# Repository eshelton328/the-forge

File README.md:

# The Forge

Hardware design monorepo for KiCad PCB projects with automated CI/CD.

## Repository Structure

```
the-forge/
├── Makefile          # make check / erc / drc / fab-drc
├── boards/           # Individual board projects
│   ├── esp32s3-devkit/        # ESP32-S3 development board
│   ├── esp32s3-devkit-5v/     # ESP32-S3 board, dual 3.3V + 5V rails (WIP)
│   └── tps63070-breakout/   # TPS63070 buck-boost breakout
├── fab-rules/        # DRC rule templates per fab house
├── kibot/            # KiBot output generation configs
├── libs/             # Shared libraries (symbols, footprints, 3D models)
├── scripts/          # Automation scripts
├── emi/              # openEMS + gerber2ems (FDTD / EMI-adjacent smoke; see emi/README.md)
└── .github/workflows # CI/CD pipelines
```

## Boards

| Board | Description | Layers | Status |
|-------|-------------|--------|--------|
| [esp32s3-devkit](boards/esp32s3-devkit/) | ESP32-S3-WROOM-1 dev board with TPS63070 buck-boost, USB-C | 4 | In Development |
| [esp32s3-devkit-5v](boards/esp32s3-devkit-5v/) | ESP32-S3 board with dual TPS63070 rails (3.3V + 5V), RV-3028 RTC, USB-C | 4 | WIP — schematic in progress |
| [tps63070-breakout](boards/tps63070-breakout/) | TPS63070 3.3V buck-boost breakout board | 2 | Migrated |

## CI/CD Pipeline

Every pull request automatically runs:
- **PR title** must follow [Conventional Commits](https://www.conventionalcommits.org/) (e.g. `feat:`, `fix:`, `chore:`, `ci:`)
- **`pytest`** on `tests/` (Python **3.12**; see [`.github/workflows/pytest.yml`](.github/workflows/pytest.yml) — Spice integration cases skip unless `ngspice`/Docker exist)
- **Open-source EMS (openEMS + gerber2ems)** — optional path-filtered workflow ([`.github/workflows/emi-checks.yml`](.github/workflows/emi-checks.yml)): builds pinned **openEMS** + **gerber2ems** and runs an upstream example slice ([`emi/README.md`](emi/README.md)); not every PR
- **ERC** (Electrical Rules Check) on schematics
- **DRC** (Design Rules Check) against multiple fab house rules (JLCPCB, PCBWay)

The KiCad workflow always runs, but it only **executes** ERC/DRC for boards that are in scope: changes under `boards/<name>/` check only those boards, while changes to `libs/`, `fab-rules/`, `kibot/`, `scripts/`, the root `Makefile`, or `.github/workflows/pr-checks.yml` trigger checks on all boards. Doc-only diffs (e.g. just `README.md`) skip the heavy KiCad jobs to save time. **`pytest`** (see **`pytest.yml`**) runs on every PR regardless, so Python regressions cannot slip through doc-only merges.

On release tags, the pipeline generates:
- Fab-ready Gerber/drill ZIPs per fab house
- BOM and component placement files
- Schematic PDFs and board renders

## Local Development

### Prerequisites

```bash
brew install --cask kicad    # KiCad 10 (includes kicad-cli)
pip install kibot kikit       # Automation tools
```

### Running checks locally

From the repository root, the **Makefile** is the usual entry point. **Each command checks one board** — the one named by `BOARD` (default: `esp32s3-devkit`). Nothing scans every board unless you ask for that explicitly.

```bash
make help           # list targets
make list-boards    # show board folder names you can pass as BOARD=...

# Default single board (esp32s3-devkit)
make check
make drc

# A different board — either form (folder and .kicad_* basename must match)
make drc BOARD=other-board
make drc other-board
make check other-board

# Optional: run make check for every board under boards/ (e.g. before a release)
make check-all
```

`kicad-cli` is picked up from your `PATH` if present; on macOS it falls back to
`/Applications/KiCad/KiCad.app/Contents/MacOS/kicad-cli`. Override with
`KICAD_CLI=/path/to/kicad-cli make check`.

### Python tests (pytest)

```bash
pip install -r requirements.txt
python3 -m pytest tests/
```

With **`ngspice`** and **Docker** available, `tests/test_spice_run_sim_integration.py` runs end-to-end Spice smoke; otherwise those cases are **skipped** (same as default CI for `pytest.yml`).

**SPICE / simulation (boards with `sim.yml`):** CI builds [`sim/docker/Dockerfile`](sim/docker/Dockerfile) — same KiCad digest as ERC/DRC plus pinned **ngspice** and the repo **`requirements.txt`** — and runs export + `run_sim.py` inside that image ([`sim/README.md`](sim/README.md)). Local parity: **`make sim-board-docker BOARD=tps63070-breakout`** or **`scripts/sim/run-spice-in-docker.sh --board …`**.

Raw commands (equivalent to the Makefile):

```bash
kicad-cli sch erc --exit-code-violations --format json -o boards/esp32s3-devkit/erc.json \
  boards/esp32s3-devkit/esp32s3-devkit.kicad_sch

kicad-cli pcb drc --exit-code-violations --refill-zones --schematic-parity --format json \
  -o boards/esp32s3-devkit/drc-default.json boards/esp32s3-devkit/esp32s3-devkit.kicad_pcb

./scripts/run-drc-all-fabs.sh boards/esp32s3-devkit
```

### Adding a new board

1. Create a new directory under `boards/`
2. Add a `board.yml` with layer count and fab targets
3. If using shared libraries, create project-local `fp-lib-table` / `sym-lib-table` pointing to `../../libs/`
4. Push a PR -- CI will automatically run checks

## Fab House Rules

DRC rules for each fab house are stored in `fab-rules/` as `.kicad_dru` files. CI swaps these in and runs DRC to tell you which fabs your design is compatible with.

2-layer and 4-layer rules each come in two tiers where noted: **standard** (baseline process) vs **advanced** (tighter vias/clearances, typically higher cost). Each board declares which rule keys it runs in `board.yml`.

| Fab House | Rule File | Notes |
|-----------|-----------|-------|
| JLCPCB 2L Standard | `jlcpcb-2layer-standard.kicad_dru` | 0.3mm via drill, 0.15mm annular ring |
| JLCPCB 2L Advanced | `jlcpcb-2layer-advanced.kicad_dru` | 0.2mm via drill, 0.1mm annular ring |
| JLCPCB 4L Standard | `jlcpcb-4layer.kicad_dru` | |
| JLCPCB 4L Advanced | `jlcpcb-4layer-advanced.kicad_dru` | Tighter annular / hole clearance / pad-track clearance vs standard 4L |
| PCBWay 2L Standard | `pcbway-2layer-standard.kicad_dru` | 0.3mm via drill, 0.45mm via pad |
| PCBWay 2L Advanced | `pcbway-2layer-advanced.kicad_dru` | 0.2mm via drill, 0.35mm via pad |
| PCBWay 4L Standard | `pcbway-4layer.kicad_dru` | |
| PCBWay 4L Advanced | `pcbway-4layer-advanced.kicad_dru` | 0.2mm via drill, 0.35mm via pad vs standard 4L |

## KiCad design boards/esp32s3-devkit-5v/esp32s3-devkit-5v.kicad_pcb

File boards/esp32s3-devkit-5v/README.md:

# ESP32-S3 DevKit with switched 5 V audio rail

Fully routed **64 × 56 mm, four-layer engineering prototype**, revised 2026-09-04. The compact layout is **35.42% smaller** than the previous 74 × 75 mm board. The four buttons retain 15 mm spacing and the component-side order **VOL− / MODE / VOL+ / BATTERY**.

Battery J1 feeds an AO3401A reverse-polarity stage and two TPS63070 buck-boost regulators: 3.307 V for the ESP32-S3/RTC and 4.985 V for the MAX98357A amplifier. GPIO18 enables the audio rail. USB-C is data-only. The RTC, switched OLED bus, wake buttons and common-anode RGB indicator remain.

The converter cells keep the nearest input/output ceramics beside the power pins, with their ground pads facing north. Their power-pad centers are 1.81 mm from VIN/VOUT, with direct 0.4 mm top-side connections. Explicit quiet feedback/VAUX returns and two nearby PGND plane connections per converter are retained. The amplifier sits beside the speaker connector. Both speaker traces are 5.37 mm long, entirely on F.Cu, with 0.6 mm main conductors and short 0.2 mm package escapes; neither uses vias. In1.Cu remains the ground reference.

New monitoring hardware provides positive USB-presence detection on GPIO7, switched battery-voltage sensing on GPIO2/ADC1 with GPIO12 enable, and converter power-good inputs on GPIO15/13. Both PG pull-ups use 3.3 V. Eight labeled underside test pads expose ground, protected battery, both rails, enables and power-good signals. SW1 now consistently specifies MSK12C02. Board-local overhang footprint variants eliminate the previous library warnings.

- [Design review, sources, firmware sequencing and remaining release work](review/design-review.md)
- [Battery measurement details](review/battery-sensing.md) and [GPIO map](review/gpio-map.csv)
- [Two-page schematic PDF](review/schematic.pdf)
- [Top render](review/pcb-preview.png), [perspective render](review/pcb-3d-perspective.png), [bottom render](docs/pcb-bottom.png), [assembly STEP](review/esp32s3-devkit-5v-assembly.step)
- [Component inventory](review/component-inventory.csv) and [3D model provenance](3dmodels/README.md)
- [Verification summary](review/verification-summary.json), [layout checks](review/layout-validation.json), [monitoring checks](review/monitoring-validation.json), [SPICE report](docs/spice-report.md)

Verified: **0 ERC violations; 0 DRC violations including warnings; 0 unconnected items; 0 schematic parity issues.** All **342 checked pad nodes across 70 nets** have saved copper. Board intent checks, the JLCPCB four-layer advanced rule profile, all 25 simulation measures, six monitoring scenarios and 80 Python tests pass (one integration test skipped). All 112 electrical footprints have local models; J1/J3/U5/U6 use documented approximations. These checks do not establish thermal, RF, USB compliance or battery endurance performance.

**Physical screening update:** the [full test report](review/physical-validation/report.md), [machine-readable results](review/physical-validation/summary.json), [raw solver data](review/physical-validation/raw-data.zip) and [free-tool runbook](../../scripts/physics/README.md) now cover PCB-only parasitics, passive supply impedance, bounded ringing, differential conducted-noise transfer and comparative PCB temperature. The compact board is **8.4 C warmer** than the original in the reference thermal scenario. A higher-loss, weak-cooling case reaches **132.8 C modeled PCB temperature at 50 C ambient**. These are assumed operating conditions, not measurements or junction temperatures. Copper inductance changes **21.6-31.8% on mesh refinement**, so its convergence gate remains open. **Physical release is not approved.** Confirm loads, cooling, stackup and component models before fabrication; green CI means the screening executes, not that these physical gates are waived.

Battery chemistry, speaker/load limits and final mechanics remain provisional. The measurement circuit is designed for a protected battery node up to 6 V; it is not a fuel gauge, charger or battery protection circuit. Before ordering, confirm the battery/load envelope, capacitor MPNs and effective capacitance, fabricator stackup/USB impedance, thermal-via assembly process and enclosure fit. The existing capacitance budget is retained.

The native KiCad files are authoritative. Placement generation replaces the PCB and requires routing, cleanup, saved zone fill, checks and visual review again. `generate_pcb.py`, `route_pcb.py`, `finalize_pcb.py` and `attach_3d_models.py` record that workflow. Use KiCad Python for PCB tools; compile `tools/grid_search.cpp` to `/tmp/esp32_grid_search.dylib` on macOS for routing. Run cleanup/fill and DRC until no newly exposed unused stubs remain.

From this directory, after schematic edits:

```sh
kicad-cli sch export netlist --format kicadxml -o review/netlist.xml esp32s3-devkit-5v.kicad_sch
python3 tools/check_netlist.py
python3 tools/check_monitoring.py
kicad-cli sch erc --format json --exit-code-violations -o review/erc.json esp32s3-devkit-5v.kicad_sch
kicad-cli pcb drc --refill-zones --schematic-parity --format json --exit-code-violations -o review/drc.json esp32s3-devkit-5v.kicad_pcb
```

Run `tools/check_layout.py` and the repository's `scripts/ci/check_copper_connectivity.py` under KiCad Python after saving filled zones. From the repository root, run `python3 scripts/validate_board.py boards/esp32s3-devkit-5v`, `python3 scripts/sim/export_kicad_spice.py --board-dir boards/esp32s3-devkit-5v`, and `python3 scripts/sim/run_sim.py --config boards/esp32s3-devkit-5v/sim.yml`. Simulation exports are regenerated from the schematic.

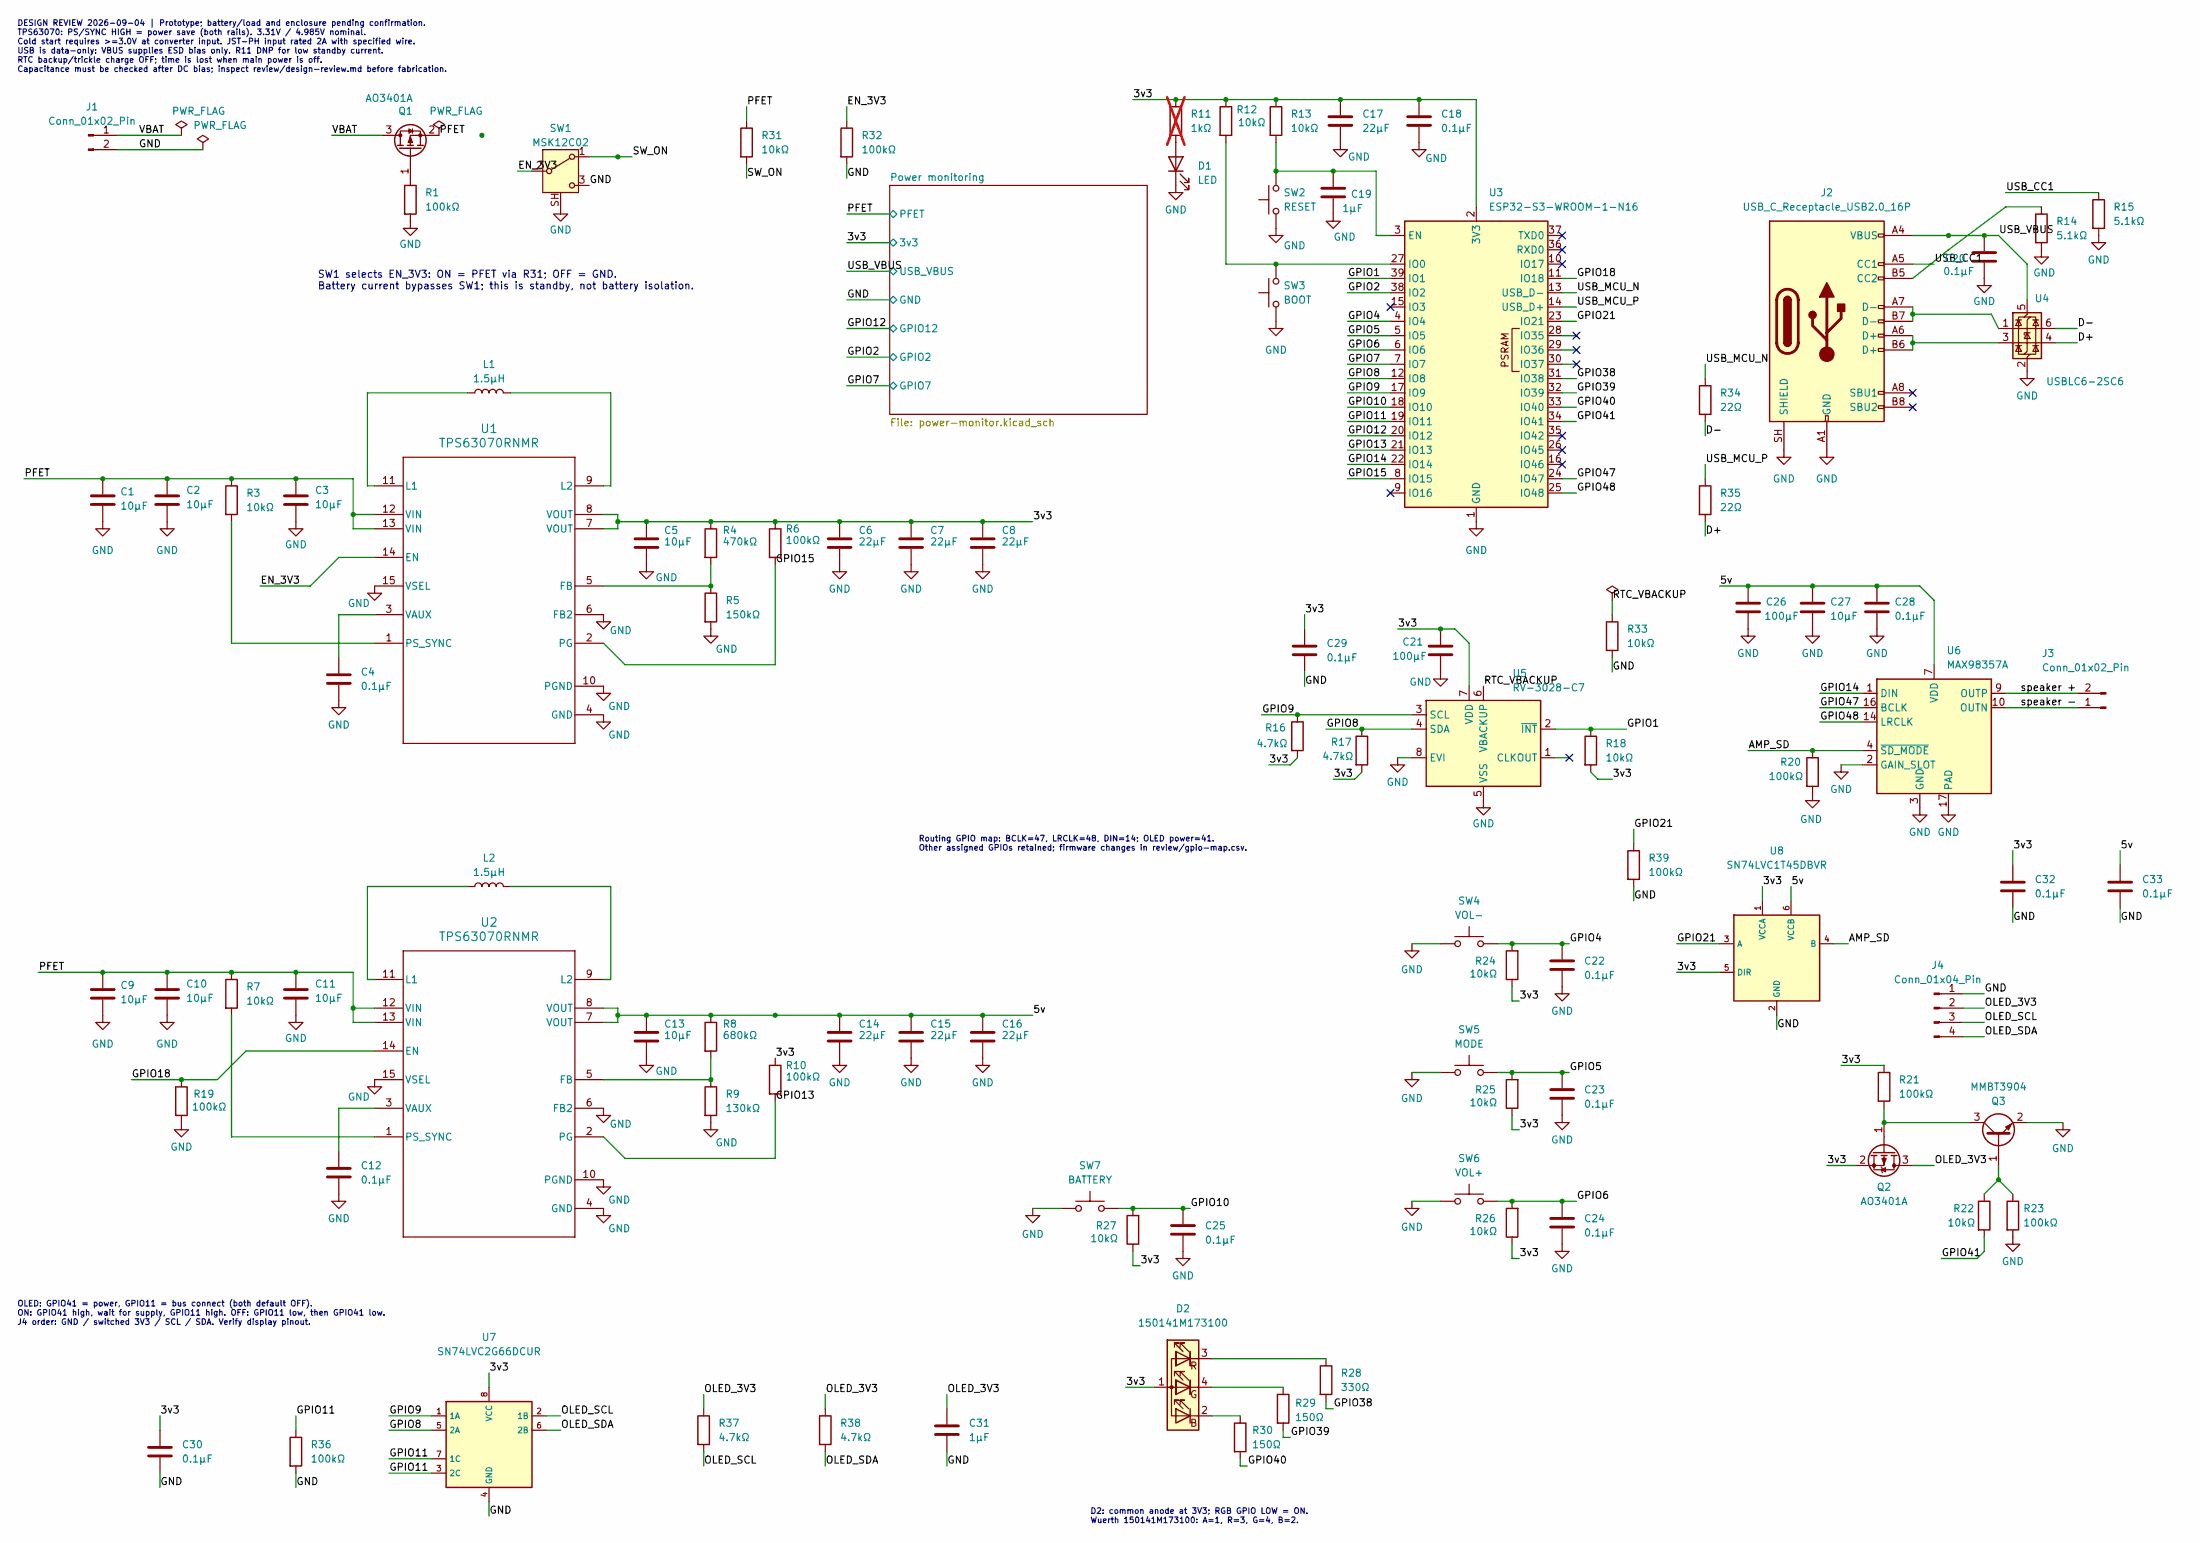
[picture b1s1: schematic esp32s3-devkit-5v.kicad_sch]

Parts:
C1, C2, C9, C10, C27: 10µF; C_0805_2012Metric; Voltage 10V minimum
C3, C5, C11, C13: 10µF; C_0603_1608Metric; Voltage 10V minimum
C4, C12, C18, C20, C22, C23, C24, C25, C28: 0.1µF; C_0402_1005Metric; Voltage 10V minimum
C6, C7, C8, C14, C15, C16: 22µF; C_1206_3216Metric; Voltage 16V; MPN GRM31CR61C226KE15L
C17: 22µF; C_0805_2012Metric; Voltage 10V minimum
C19: 1µF; C_0402_1005Metric; Voltage 10V minimum
C21, C26: 100µF; C_1206_3216Metric; Voltage 10V minimum
C29, C30, C32, C33: 0.1µF; C_0402_1005Metric
C31: 1µF; C_0603_1608Metric
D1: LED; LED_0603_1608Metric
D2: 150141M173100; LED_RGB_Wuerth-PLCC4_3.2x2.8mm_150141M173100; MPN 150141M173100
J1: Conn_01x02_Pin; JST_PH_B2B-PH-SM4-TB_1x02-1MP_P2.00mm_Vertical
J2: USB_C_Receptacle_USB2.0_16P; USB_C_HRO_Overhang
J3: Conn_01x02_Pin; JST_PH_Speaker_Overhang
J4: Conn_01x04_Pin; PinHeader_1x04_P2.54mm_Vertical
L1, L2: 1.5µH; IND_XFL4020-152MEC; MPN XFL4020-152MEC
Q1, Q2: AO3401A; SOT-23
Q3: MMBT3904; SOT-23
R1, R6, R10, R19, R20, R21, R23, R32, R36, R39: 100kΩ; R_0402_1005Metric
R3, R7, R12, R13, R18, R22, R24, R25, R26, R27, R31, R33: 10kΩ; R_0402_1005Metric
R4: 470kΩ; R_0402_1005Metric; Tolerance 1%
R5: 150kΩ; R_0402_1005Metric; Tolerance 1%
R8: 680kΩ; R_0402_1005Metric; Tolerance 1%
R9: 130kΩ; R_0402_1005Metric; Tolerance 1%
R11: 1kΩ; R_0402_1005Metric; not fitted
R14, R15: 5.1kΩ; R_0402_1005Metric; Tolerance 1%
R16, R17, R37, R38: 4.7kΩ; R_0402_1005Metric
R28: 330Ω; R_0402_1005Metric
R29, R30: 150Ω; R_0402_1005Metric
R34, R35: 22Ω; R_0402_1005Metric
SW1: MSK12C02; SW_SPDT_Shouhan_MSK12C02; MPN MSK12C02
SW2: RESET; SW_Push_1P1T_XKB_TS-1187A
SW3: BOOT; SW_Push_1P1T_XKB_TS-1187A
SW4: VOL-; SW_Push_1P1T_XKB_TS-1187A
SW5: MODE; SW_Push_1P1T_XKB_TS-1187A
SW6: VOL+; SW_Push_1P1T_XKB_TS-1187A
SW7: BATTERY; SW_Push_1P1T_XKB_TS-1187A
U1, U2: TPS63070RNMR; TPS63070
U3: ESP32-S3-WROOM-1-N16; ESP32-S3-WROOM-1_Overhang
U4: USBLC6-2SC6; SOT-23-6
U5: RV-3028-C7; MicroCrystal_C7_SON-8_1.5x3.2mm_P0.9mm
U6: MAX98357A; TQFN-16-1EP_3x3mm_P0.5mm_EP1.23x1.23mm
U7: SN74LVC2G66DCUR; VSSOP-8_2.3x2mm_P0.5mm
U8: SN74LVC1T45DBVR; SOT-23-6

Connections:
/3v3: C5.1, C6.1, C7.1, C8.1, C17.1, C18.1, C21.1, C29.1, C30.1, C32.1, D2.1 (A), Q2.2 (S), R4.1, R6.1, R10.1, R11.1, R12.1, R13.1, R16.2, R17.2, R18.2, R21.1, R24.1, R25.1, R26.1, R27.1, U1.7 (VOUT), U1.8 (VOUT), U3.2 (3V3), U5.7 (VDD), U7.8 (VCC), U8.1 (VCCA), U8.5 (DIR); also elsewhere on the board
/5v: C13.1, C14.1, C15.1, C16.1, C26.1, C27.1, C28.1, C33.1, R8.1, U2.7 (VOUT), U2.8 (VOUT), U6.7 (VDD), U6.8 (VDD), U8.6 (VCCB); also elsewhere on the board
/AMP_SD: R20.1, U6.4 (~SD_MODE), U8.4 (B)
/D+: R35.2, U4.4 (I/O2)
/D-: R34.2, U4.6 (I/O1)
/EN_3V3: R32.1, SW1.2 (B), U1.14 (EN); also elsewhere on the board
/GPIO1: R18.1, U3.39 (IO1), U5.2 (~INT)
/GPIO2: U3.38 (IO2); also elsewhere on the board
/GPIO4: C22.1, R24.2, SW4.2, U3.4 (IO4)
/GPIO5: C23.1, R25.2, SW5.2, U3.5 (IO5)
/GPIO6: C24.1, R26.2, SW6.2, U3.6 (IO6)
/GPIO7: U3.7 (IO7); also elsewhere on the board
/GPIO8: R17.1, U3.12 (IO8), U5.4 (SDA), U7.5 (2A)
/GPIO9: R16.1, U3.17 (IO9), U5.3 (SCL), U7.1 (1A)
/GPIO10: C25.1, R27.2, SW7.2, U3.18 (IO10)
/GPIO11: R36.1, U3.19 (IO11), U7.3 (2C), U7.7 (1C)
/GPIO12: U3.20 (IO12); also elsewhere on the board
/GPIO13: R10.2, U2.2 (PG), U3.21 (IO13); also elsewhere on the board
/GPIO14: U3.22 (IO14), U6.1 (DIN)
/GPIO15: R6.2, U1.2 (PG), U3.8 (IO15); also elsewhere on the board
/GPIO18: R19.1, U2.14 (EN), U3.11 (IO18); also elsewhere on the board
/GPIO21: R39.1, U3.23 (IO21), U8.3 (A)
/GPIO38: R28.2, U3.31 (IO38)
/GPIO39: R29.2, U3.32 (IO39)
/GPIO40: R30.2, U3.33 (IO40)
/GPIO41: R22.2, U3.34 (IO41)
/GPIO47: U3.24 (IO47), U6.16 (BCLK)
/GPIO48: U3.25 (IO48), U6.14 (LRCLK)
/OLED_3V3: C31.1, J4.2, Q2.3 (D), R37.1, R38.1
/OLED_SCL: J4.3, R37.2, U7.2 (1B)
/OLED_SDA: J4.4, R38.2, U7.6 (2B)
/PFET: C1.1, C2.1, C3.1, C9.1, C10.1, C11.1, Q1.2 (S), R3.1, R7.1, R31.1, U1.12 (VIN), U1.13 (VIN), U2.12 (VIN), U2.13 (VIN); also elsewhere on the board
/RTC_VBACKUP: R33.1, U5.6 (VBACKUP)
/SW_ON: R31.2, SW1.1 (A)
/USB_CC1: J2.A5 (CC1), R15.1
/USB_MCU_N: R34.1, U3.13 (USB_D-)
/USB_MCU_P: R35.1, U3.14 (USB_D+)
/USB_VBUS: C20.1, J2.A4 (VBUS), J2.A9 (VBUS), J2.B4 (VBUS), J2.B9 (VBUS), U4.5 (VBUS); also elsewhere on the board
/VBAT: J1.1, Q1.3 (D)
/speaker +: J3.2, U6.9 (OUTP)
/speaker -: J3.1, U6.10 (OUTN)
GND: C1.2, C2.2, C3.2, C4.2, C5.2, C6.2, C7.2, C8.2, C9.2, C10.2, C11.2, C12.2, C13.2, C14.2, C15.2, C16.2, C17.2, C18.2, C19.2, C20.2, C21.2, C22.2, C23.2, C24.2, C25.2, C26.2, C27.2, C28.2, C29.2, C30.2, C31.2, C32.2, C33.2, D1.1 (K), J1.2, J2.A1 (GND), J2.A12 (GND), J2.B1 (GND), J2.B12 (GND), J2.SH (SHIELD), J4.1, Q3.2 (E), R1.2, R5.2, R9.2, R14.2, R15.2, R19.2, R20.2, R23.2, R32.2, R33.2, R36.2, R39.2, SW1.3 (C), SW1.SH, SW2.1, SW3.1, SW4.1, SW5.1, SW6.1, SW7.1, U1.4 (GND), U1.6 (FB2), U1.10 (PGND), U1.15 (VSEL), U2.4 (GND), U2.6 (FB2), U2.10 (PGND), U2.15 (VSEL), U3.1 (GND), U3.40 (GND), U3.41 (GND), U4.2 (GND), U5.5 (VSS), U5.8 (EVI), U6.2 (GAIN_SLOT), U6.3 (GND), U6.11 (GND), U6.15 (GND), U6.17 (PAD), U7.4 (GND), U8.2 (GND); also elsewhere on the board
unnamed: D1.2 (A), R11.2
unnamed: D2.2 (BK), R30.1
unnamed: D2.4 (GK), R29.1
unnamed: D2.3 (RK), R28.1
unnamed: J2.B5 (CC2), R14.1
unnamed: J2.A6 (D+), J2.B6 (D+), U4.3 (I/O2)
unnamed: J2.A7 (D-), J2.B7 (D-), U4.1 (I/O1)
unnamed: Q1.1 (G), R1.1
unnamed: Q2.1 (G), Q3.3 (C), R21.2
unnamed: Q3.1 (B), R22.1, R23.1
unnamed: R4.2, R5.1, U1.5 (FB)
unnamed: L1.1, U1.11 (L1)
unnamed: L1.2, U1.9 (L2)
unnamed: R3.2, U1.1 (PS_SYNC)
unnamed: C4.1, U1.3 (VAUX)
unnamed: R8.2, R9.1, U2.5 (FB)
unnamed: L2.1, U2.11 (L1)
unnamed: L2.2, U2.9 (L2)
unnamed: R7.2, U2.1 (PS_SYNC)
unnamed: C12.1, U2.3 (VAUX)
unnamed: C19.1, R13.2, SW2.2, U3.3 (EN)
unnamed: R12.2, SW3.2, U3.27 (IO0)

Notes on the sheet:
SW1 selects EN_3V3: ON = PFET via R31; OFF = GND. Battery current bypasses SW1; this is standby, not battery isolation.
OLED: GPIO41 = power, GPIO11 = bus connect (both default OFF). ON: GPIO41 high, wait for supply, GPIO11 high. OFF: GPIO11 low, then GPIO41 low. J4 order: GND / switched 3V3 / SCL / SDA. Verify display pinout.
D2: common anode at 3V3; RGB GPIO LOW = ON. Wuerth 150141M173100: A=1, R=3, G=4, B=2.
Routing GPIO map: BCLK=47, LRCLK=48, DIN=14; OLED power=41. Other assigned GPIOs retained; firmware changes in review/gpio-map.csv.
DESIGN REVIEW 2026-09-04 | Prototype; battery/load and enclosure pending confirmation. TPS63070: PS/SYNC HIGH = power save (both rails). 3.31V / 4.985V nominal. Cold start requires >=3.0V at converter input. JST-PH input rated 2A with specified wire. USB is data-only: VBUS supplies ESD bias only. R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

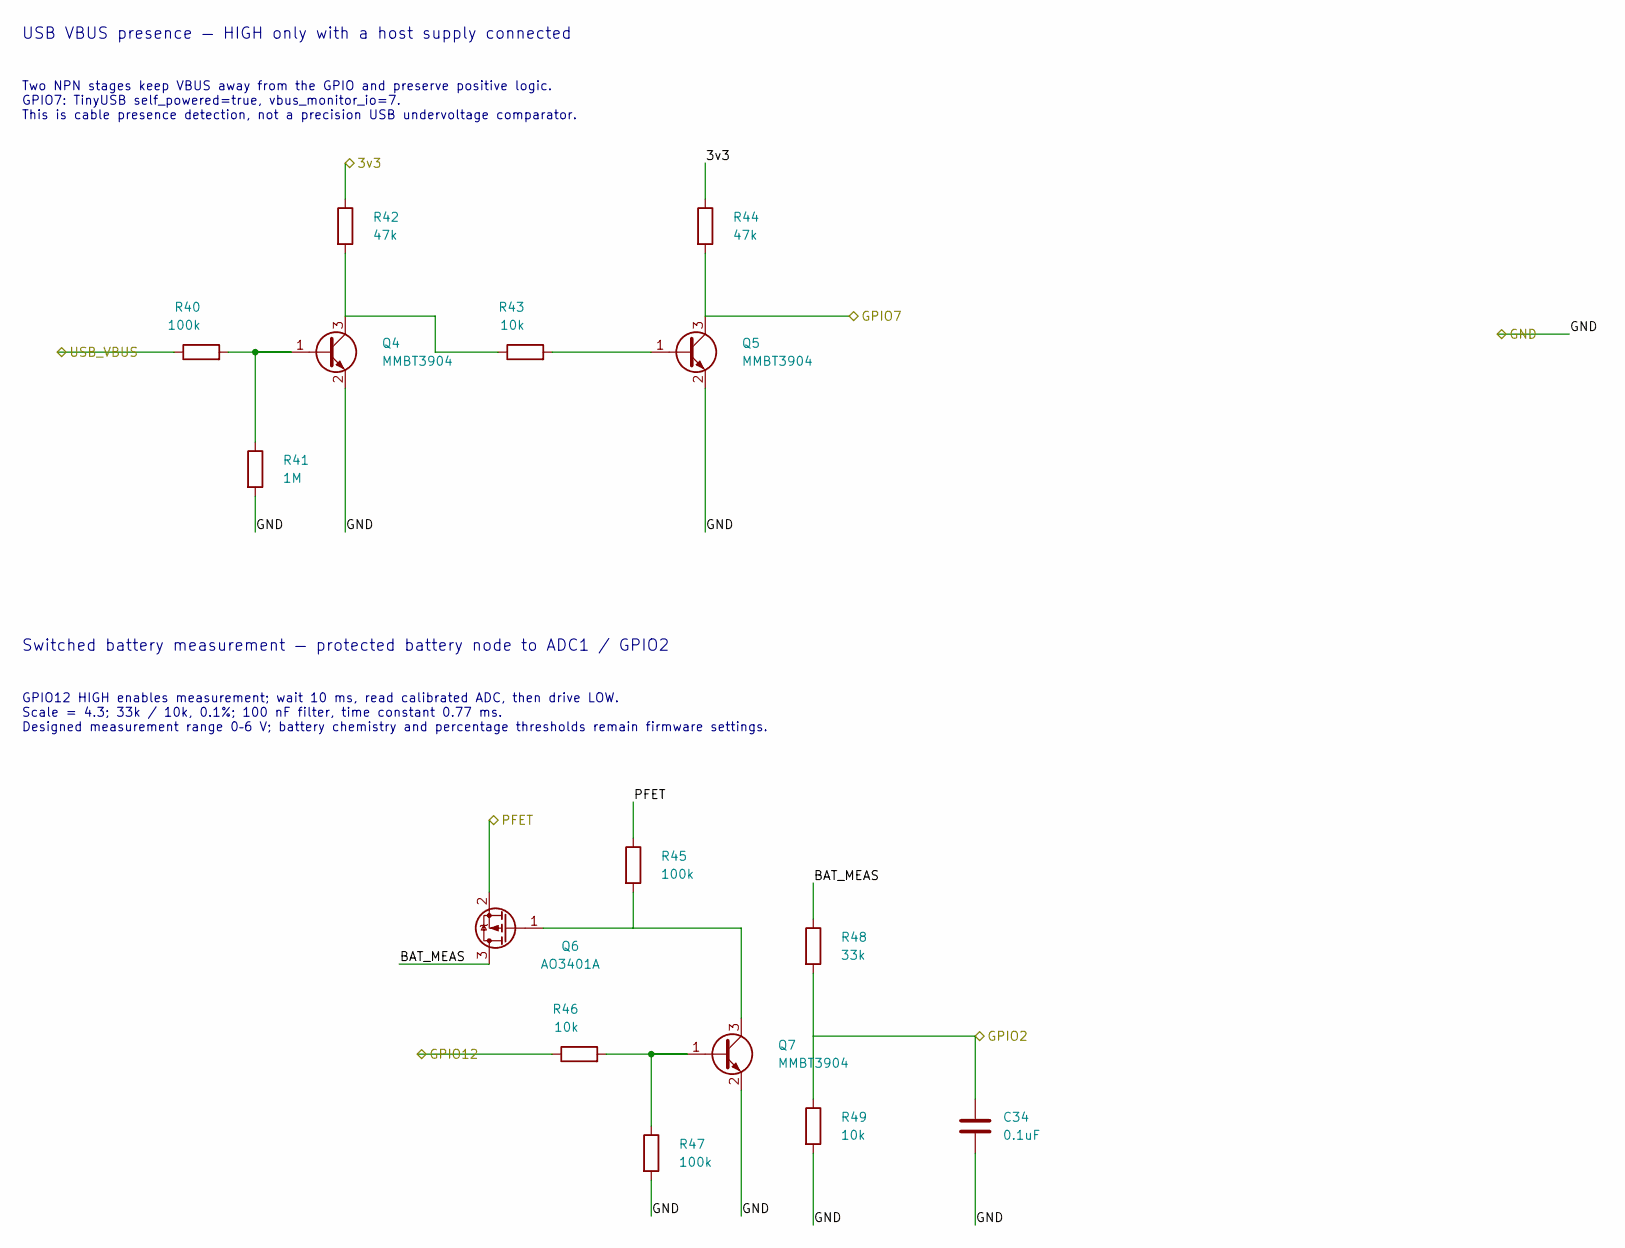
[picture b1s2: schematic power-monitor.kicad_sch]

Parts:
C34: 0.1uF; C_0402_1005Metric; Voltage 16V
Q4, Q5, Q7: MMBT3904; SOT-23
Q6: AO3401A; SOT-23
R40, R45, R47: 100k; R_0402_1005Metric
R41: 1M; R_0402_1005Metric
R42, R44: 47k; R_0402_1005Metric
R43, R46: 10k; R_0402_1005Metric
R48: 33k; R_0402_1005Metric; Tolerance 0.1%; MPN RT0402BRD0733KL
R49: 10k; R_0402_1005Metric; Tolerance 0.1%; MPN RT0402BRD0710KL

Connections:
/3v3: R42.1, R44.1; also elsewhere on the board
/GPIO2: C34.1, R48.2, R49.1; also elsewhere on the board
/GPIO7: Q5.3 (C), R44.2; also elsewhere on the board
/GPIO12: R46.1; also elsewhere on the board
/PFET: Q6.2 (S), R45.1; also elsewhere on the board
/Power monitoring/BAT_MEAS: Q6.3 (D), R48.1
/USB_VBUS: R40.1; also elsewhere on the board
GND: C34.2, Q4.2 (E), Q5.2 (E), Q7.2 (E), R41.2, R47.2, R49.2; also elsewhere on the board
unnamed: Q4.1 (B), R40.2, R41.1
unnamed: Q4.3 (C), R42.2, R43.1
unnamed: Q5.1 (B), R43.2
unnamed: Q6.1 (G), Q7.3 (C), R45.2
unnamed: Q7.1 (B), R46.2, R47.1

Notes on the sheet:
USB VBUS presence — HIGH only with a host supply connected
Two NPN stages keep VBUS away from the GPIO and preserve positive logic. GPIO7: TinyUSB self_powered=true, vbus_monitor_io=7. This is cable presence detection, not a precision USB undervoltage comparator.
Switched battery measurement — protected battery node to ADC1 / GPIO2
GPIO12 HIGH enables measurement; wait 10 ms, read calibrated ADC, then drive LOW. Scale = 4.3; 33k / 10k, 0.1%; 100 nF filter, time constant 0.77 ms. Designed measurement range 0–6 V; battery chemistry and percentage thresholds remain firmware settings.

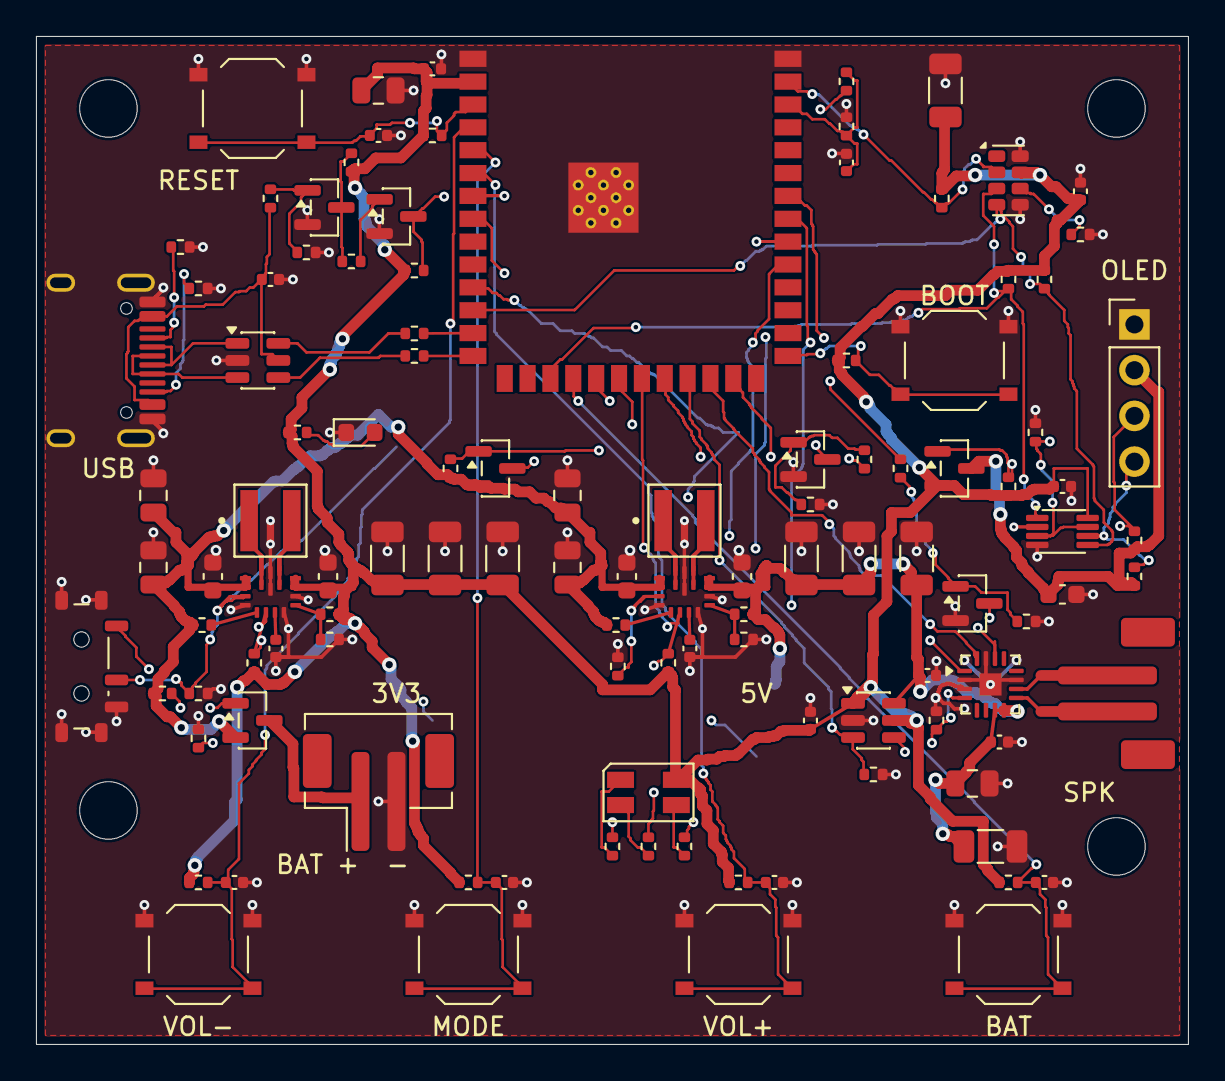
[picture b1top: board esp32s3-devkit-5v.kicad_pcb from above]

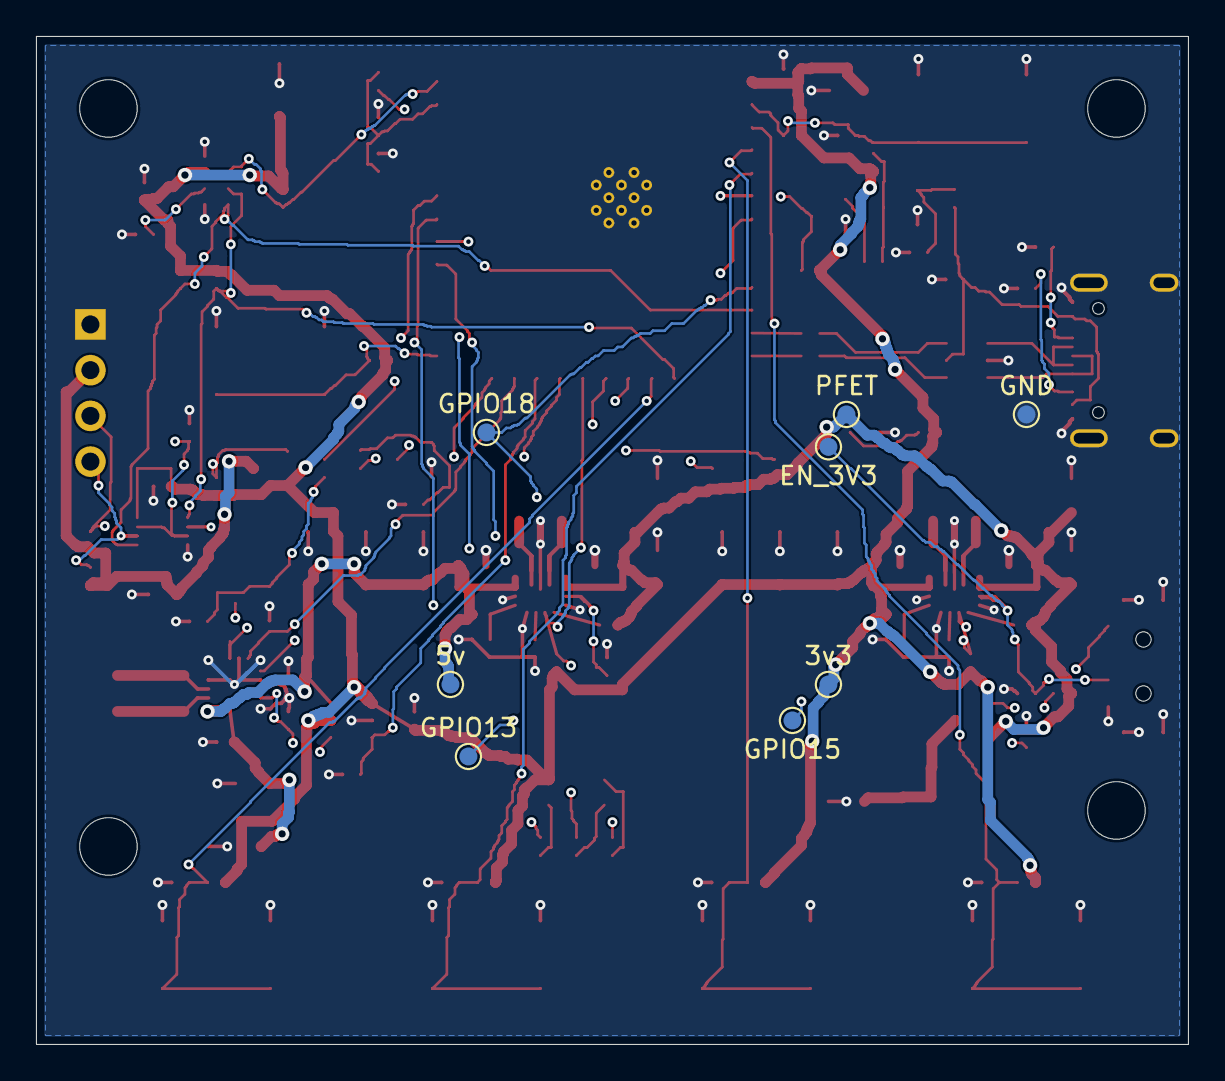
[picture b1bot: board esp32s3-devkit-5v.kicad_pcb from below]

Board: 4 copper layers, 64.0 x 56.0 mm, 124 parts (8 on the bottom side), 70 nets.

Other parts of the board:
H1, H2, H3, H4: M3; MountingHole_3.2mm_M3
TP1: GND; TestPoint_Pad_D1.0mm
TP2: PFET; TestPoint_Pad_D1.0mm
TP3: 3v3; TestPoint_Pad_D1.0mm
TP4: 5v; TestPoint_Pad_D1.0mm
TP5: GPIO15; TestPoint_Pad_D1.0mm
TP6: GPIO13; TestPoint_Pad_D1.0mm
TP7: EN_3V3; TestPoint_Pad_D1.0mm
TP8: GPIO18; TestPoint_Pad_D1.0mm

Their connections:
/3v3: TP3.1; also elsewhere on the board
/5v: TP4.1; also elsewhere on the board
/EN_3V3: TP7.1; also elsewhere on the board
/GPIO13: TP6.1; also elsewhere on the board
/GPIO15: TP5.1; also elsewhere on the board
/GPIO18: TP8.1; also elsewhere on the board
/PFET: TP2.1; also elsewhere on the board
GND: TP1.1; also elsewhere on the board

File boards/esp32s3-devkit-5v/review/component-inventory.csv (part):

Reference,Value,Footprint,MPN field,Datasheet,DNP,Procurement status
C1,10µF,Capacitor_SMD:C_0805_2012Metric,,,False,MPN selection still required; verify rating/tolerance/DC bias
C10,10µF,Capacitor_SMD:C_0805_2012Metric,,,False,MPN selection still required; verify rating/tolerance/DC bias
C11,10µF,Capacitor_SMD:C_0603_1608Metric,,,False,MPN selection still required; verify rating/tolerance/DC bias
C12,0.1µF,Capacitor_SMD:C_0402_1005Metric,,,False,MPN selection still required; verify rating/tolerance/DC bias
C13,10µF,Capacitor_SMD:C_0603_1608Metric,,,False,MPN selection still required; verify rating/tolerance/DC bias
C14,22µF,Capacitor_SMD:C_1206_3216Metric,GRM31CR61C226KE15L,https://search.murata.co.jp/Ceramy/image/img/A01X/G101/ENG/G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,False,MPN specified; verify availability and ordered suffix
C15,22µF,Capacitor_SMD:C_1206_3216Metric,GRM31CR61C226KE15L,https://search.murata.co.jp/Ceramy/image/img/A01X/G101/ENG/G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,False,MPN specified; verify availability and ordered suffix
C16,22µF,Capacitor_SMD:C_1206_3216Metric,GRM31CR61C226KE15L,https://search.murata.co.jp/Ceramy/image/img/A01X/G101/ENG/G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,False,MPN specified; verify availability and ordered suffix
C17,22µF,Capacitor_SMD:C_0805_2012Metric,,,False,MPN selection still required; verify rating/tolerance/DC bias
C18,0.1µF,Capacitor_SMD:C_0402_1005Metric,,,False,MPN selection still required; verify rating/tolerance/DC bias
C19,1µF,Capacitor_SMD:C_0402_1005Metric,,,False,MPN selection still required; verify rating/tolerance/DC bias
C2,10µF,Capacitor_SMD:C_0805_2012Metric,,,False,MPN selection still required; verify rating/tolerance/DC bias
C20,0.1µF,Capacitor_SMD:C_0402_1005Metric,,,False,MPN selection still required; verify rating/tolerance/DC bias
C21,100µF,Capacitor_SMD:C_1206_3216Metric,,,False,MPN selection still required; verify rating/tolerance/DC bias
C22,0.1µF,Capacitor_SMD:C_0402_1005Metric,,,False,MPN selection still required; verify rating/tolerance/DC bias
C23,0.1µF,Capacitor_SMD:C_0402_1005Metric,,,False,MPN selection still required; verify rating/tolerance/DC bias
C24,0.1µF,Capacitor_SMD:C_0402_1005Metric,,,False,MPN selection still required; verify rating/tolerance/DC bias
C25,0.1µF,Capacitor_SMD:C_0402_1005Metric,,,False,MPN selection still required; verify rating/tolerance/DC bias
C26,100µF,Capacitor_SMD:C_1206_3216Metric,,,False,MPN selection still required; verify rating/tolerance/DC bias
C27,10µF,Capacitor_SMD:C_0805_2012Metric,,,False,MPN selection still required; verify rating/tolerance/DC bias
C28,0.1µF,Capacitor_SMD:C_0402_1005Metric,,,False,MPN selection still required; verify rating/tolerance/DC bias
C29,0.1µF,Capacitor_SMD:C_0402_1005Metric,,,False,MPN selection still required; verify rating/tolerance/DC bias
C3,10µF,Capacitor_SMD:C_0603_1608Metric,,,False,MPN selection still required; verify rating/tolerance/DC bias
C30,0.1µF,Capacitor_SMD:C_0402_1005Metric,,,False,MPN selection still required; verify rating/tolerance/DC bias
C31,1µF,Capacitor_SMD:C_0603_1608Metric,,,False,MPN selection still required; verify rating/tolerance/DC bias
C32,0.1µF,Capacitor_SMD:C_0402_1005Metric,,,False,MPN selection still required; verify rating/tolerance/DC bias
C33,0.1µF,Capacitor_SMD:C_0402_1005Metric,,,False,MPN selection still required; verify rating/tolerance/DC bias
C34,0.1uF,Capacitor_SMD:C_0402_1005Metric,,,False,MPN selection still required; verify rating/tolerance/DC bias
C4,0.1µF,Capacitor_SMD:C_0402_1005Metric,,,False,MPN selection still required; verify rating/tolerance/DC bias
C5,10µF,Capacitor_SMD:C_0603_1608Metric,,,False,MPN selection still required; verify rating/tolerance/DC bias
C6,22µF,Capacitor_SMD:C_1206_3216Metric,GRM31CR61C226KE15L,https://search.murata.co.jp/Ceramy/image/img/A01X/G101/ENG/G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,False,MPN specified; verify availability and ordered suffix
C7,22µF,Capacitor_SMD:C_1206_3216Metric,GRM31CR61C226KE15L,https://search.murata.co.jp/Ceramy/image/img/A01X/G101/ENG/G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,False,MPN specified; verify availability and ordered suffix
C8,22µF,Capacitor_SMD:C_1206_3216Metric,GRM31CR61C226KE15L,https://search.murata.co.jp/Ceramy/image/img/A01X/G101/ENG/G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,False,MPN specified; verify availability and ordered suffix
C9,10µF,Capacitor_SMD:C_0805_2012Metric,,,False,MPN selection still required; verify rating/tolerance/DC bias
D1,LED,LED_SMD:LED_0603_1608Metric,,,False,Verify final vendor/package/assembly details
D2,150141M173100,LED_SMD:LED_RGB_Wuerth-PLCC4_3.2x2.8mm_150141M173100,150141M173100,https://www.we-online.com/components/products/datasheet/1501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,False,MPN specified; verify availability and ordered suffix
J1,Conn_01x02_Pin,Connector_JST:JST_PH_B2B-PH-SM4-TB_1x02-1MP_P2.00mm_Vertical,,https://www.jst-mfg.com/product/pdf/eng/ePH.pdf,False,Verify final vendor/package/assembly details
J2,USB_C_Receptacle_USB2.0_16P,Board:USB_C_HRO_Overhang,,https://www.usb.org/sites/default/files/documents/usb_type-c.zip,False,Verify final vendor/package/assembly details
J3,Conn_01x02_Pin,Board:JST_PH_Speaker_Overhang,,https://www.jst-mfg.com/product/pdf/eng/ePH.pdf,False,Verify final vendor/package/assembly details
J4,Conn_01x04_Pin,Connector_PinHeader_2.54mm:PinHeader_1x04_P2.54mm_Vertical,,,False,Verify final vendor/package/assembly details
L1,1.5µH,TPS63070:IND_XFL4020-152MEC,XFL4020-152MEC,https://www.coilcraft.com/en-us/products/power/shielded-indu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,False,MPN specified; verify availability and ordered suffix
L2,1.5µH,TPS63070:IND_XFL4020-152MEC,XFL4020-152MEC,https://www.coilcraft.com/en-us/products/power/shielded-indu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,False,MPN specified; verify availability and ordered suffix
Q1,AO3401A,Package_TO_SOT_SMD:SOT-23,,https://www.aosmd.com/sites/default/files/res/datasheets/AO3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,False,Verify final vendor/package/assembly details
Q2,AO3401A,Package_TO_SOT_SMD:SOT-23,,https://www.aosmd.com/sites/default/files/res/datasheets/AO3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,False,Verify final vendor/package/assembly details
Q3,MMBT3904,Package_TO_SOT_SMD:SOT-23,,https://www.onsemi.com/pdf/datasheet/mmbt3904lt1-d.pdf,False,Verify final vendor/package/assembly details
Q4,MMBT3904,Package_TO_SOT_SMD:SOT-23,,https://www.onsemi.com/pdf/datasheet/mmbt3904lt1-d.pdf,False,Verify final vendor/package/assembly details
Q5,MMBT3904,Package_TO_SOT_SMD:SOT-23,,https://www.onsemi.com/pdf/datasheet/mmbt3904lt1-d.pdf,False,Verify final vendor/package/assembly details
Q6,AO3401A,Package_TO_SOT_SMD:SOT-23,,https://www.aosmd.com/sites/default/files/res/datasheets/AO3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,False,Verify final vendor/package/assembly details
Q7,MMBT3904,Package_TO_SOT_SMD:SOT-23,,https://www.onsemi.com/pdf/datasheet/mmbt3904lt1-d.pdf,False,Verify final vendor/package/assembly details
R1,100kΩ,Resistor_SMD:R_0402_1005Metric,,,False,Verify final vendor/package/assembly details
R10,100kΩ,Resistor_SMD:R_0402_1005Metric,,,False,Verify final vendor/package/assembly details
R11,1kΩ,Resistor_SMD:R_0402_1005Metric,,,True,Verify final vendor/package/assembly details
R12,10kΩ,Resistor_SMD:R_0402_1005Metric,,,False,Verify final vendor/package/assembly details
R13,10kΩ,Resistor_SMD:R_0402_1005Metric,,,False,Verify final vendor/package/assembly details
R14,5.1kΩ,Resistor_SMD:R_0402_1005Metric,,,False,Verify final vendor/package/assembly details
R15,5.1kΩ,Resistor_SMD:R_0402_1005Metric,,,False,Verify final vendor/package/assembly details
R16,4.7kΩ,Resistor_SMD:R_0402_1005Metric,,,False,Verify final vendor/package/assembly details
R17,4.7kΩ,Resistor_SMD:R_0402_1005Metric,,,False,Verify final vendor/package/assembly details
R18,10kΩ,Resistor_SMD:R_0402_1005Metric,,,False,Verify final vendor/package/assembly details
R19,100kΩ,Resistor_SMD:R_0402_1005Metric,,,False,Verify final vendor/package/assembly details
R20,100kΩ,Resistor_SMD:R_0402_1005Metric,,,False,Verify final vendor/package/assembly details
R21,100kΩ,Resistor_SMD:R_0402_1005Metric,,,False,Verify final vendor/package/assembly details
R22,10kΩ,Resistor_SMD:R_0402_1005Metric,,,False,Verify final vendor/package/assembly details
R23,100kΩ,Resistor_SMD:R_0402_1005Metric,,,False,Verify final vendor/package/assembly details
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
